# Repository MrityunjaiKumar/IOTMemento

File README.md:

# IOTMemento

## Introduction
This hardware was fabricated for AICTE Idea Lab FDP held at TI-CEPD, NSUT.
This repository is hosting tempalte code with Pinmapping and libraries information used during FDP. 
Also, An Android app is provided to view the data of the temperature form the hardware.
Features of this device are as follows:- 
1. Before wifi provisioning :- 

*  Rainbow pattern on RGB
*  Every 10 seconds all 12 petal leds will glow in linear fashion.

2. After wifi provisioning

* Rainbow pattern on RGB
* Play mario death tone every hour at 00 minute.
* Each of 12 petal leds will glow one after another in clockwise fashion, denoting complition of 5 minutes.
* Temperature sent to sincgrid cloud and data will be visible on sincgrid home app

### Design files

Editable files are located in Hardware folder

### Android APP
There is an Android application available at the play store for provisioning of the device (i.e. providing wifi ssid and passsword) and relaying the information.

Application can be located at https://play.google.com/store/apps/details?id=com.sincgrid.sincgridhome

Below are the steps needed to commision the device
1. Regsiter user
2. WiFi provision of the device
3. Regualr temperature update on the card

#### Registering the user
* After opening the app, Click on the Register button. 

* Fill in the details

* On provided email id, an OTP will be send. 

* After confirming the OTP you will be logged in into the application.

#### WiFi provision of the device

* On App side Click on the add button to start provisioning

* On device side, Press the button for 5 second, you will hear a buzzer beep that mark as confirmation of initiation of provisioning.

* To whatever the wifi you phone is connected, that SSID will be taken by default. To change this, you can switch the wifi form the phone.

* Please provide the credentials of the the ssid.

After this app will automatically add the device.

#### Regualr temperature update on the card
After every 15 minutes device will send the temperature data from LM75.

## Libraries used during FDP are :- 

* [esp32-Encrypt](https://github.com/josephpal/esp32-Encrypt.git)
* bblanchon/ArduinoJson
* [ESPAsyncWebServer](https://github.com/me-no-dev/ESPAsyncWebServer.git)
* [AsyncTCP](https://github.com/me-no-dev/AsyncTCP.git)
* [ESP32_AnalogWrite](https://github.com/ERROPiX/ESP32_AnalogWrite.git)
* [NTPClient](https://github.com/MrityunjaiKumar/NTPClient.git)
* [Tone](https://github.com/lbernstone/Tone.git)
* PubSubClient

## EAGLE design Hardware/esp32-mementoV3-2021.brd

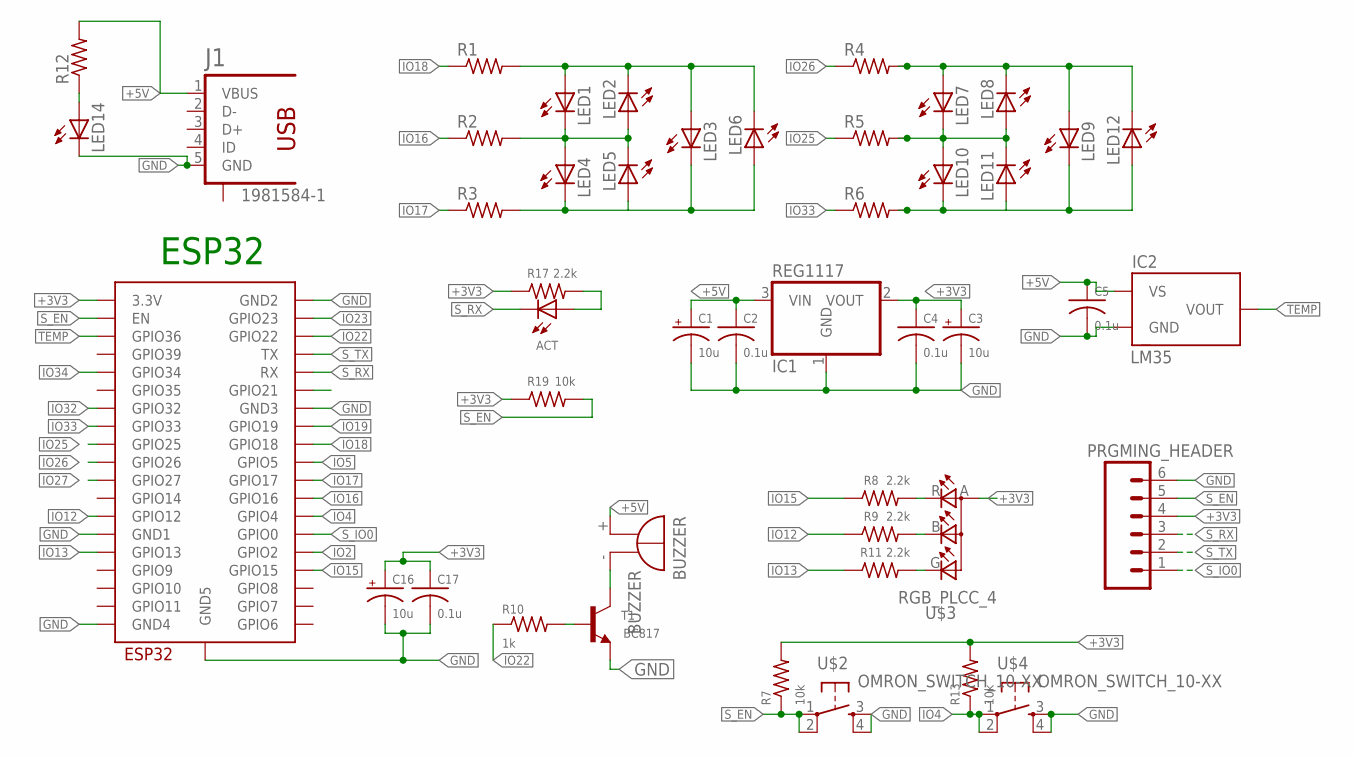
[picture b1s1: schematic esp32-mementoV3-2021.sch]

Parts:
ACT: LEDCHIPLED_1206; CHIPLED_1206
BUZZER: BUZZER; F/TMB
C1, C3, C16: 10u; B/3528-21R
C2, C4, C5, C17: 0.1u; C0603
ESP32_MODULE: ESP32-WROOM
IC1: REG1117; SOT223
IC2: LM35; TO92
J1: 1981584-1
LED1, LED2, LED3, LED4, LED5, LED6, LED7, LED8, LED9, LED10, LED11, LED12, LED14: LED1206; CHIPLED_1206
PRGMING_HEADER: M06; 06P
R1, R2, R3, R4, R5, R6, R12: RESISTOR0805; R0805
R7, R13: 10k; M0805
R8, R9, R11, R17: 2.2k; R0805
R10: 1k; M0805
R19: 10k; R0805
T1: BC817; SOT23-BEC
U$2, U$4: OMRON_SWITCH_10-XX; B3F-10XX
U$3: RGB_PLCC_4; PLCC-4

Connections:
+3V3: C3.+, C4.1, C16.+, C17.1, ESP32_MODULE.3V3 (3.3V), IC1.2 (VOUT), PRGMING_HEADER.4, R7.2, R13.2, R17.1, R19.1, U$3.A (A2)
+5V: BUZZER.+, C1.+, C2.1, C5.1, IC1.3 (VIN), IC2.VS, J1.1 (VBUS), R12.2
GND: C1.-, C2.2, C3.-, C4.2, C5.2, C16.-, C17.2, ESP32_MODULE.GND1, ESP32_MODULE.GND2, ESP32_MODULE.GND3, ESP32_MODULE.GND4, ESP32_MODULE.GND5, IC1.1 (GND), IC2.GND, J1.5 (GND), LED14.C, PRGMING_HEADER.6, T1.E, U$2.3 (S), U$2.4 (S1), U$4.3 (S), U$4.4 (S1)
IO2: ESP32_MODULE.IO2 (GPIO2)
IO4: ESP32_MODULE.IO4 (GPIO4), R13.1, U$4.1, U$4.2 (P1)
IO5: ESP32_MODULE.IO5 (GPIO5)
IO12: ESP32_MODULE.IO12 (GPIO12), R9.1
IO13: ESP32_MODULE.IO13 (GPIO13), R11.1
IO15: ESP32_MODULE.IO15 (GPIO15), R8.1
IO16: ESP32_MODULE.IO16 (GPIO16), R2.1
IO17: ESP32_MODULE.IO17 (GPIO17), R3.1
IO18: ESP32_MODULE.IO18 (GPIO18), R1.1
IO19: ESP32_MODULE.IO19 (GPIO19)
IO22: ESP32_MODULE.IO22 (GPIO22), R10.1
IO23: ESP32_MODULE.IO23 (GPIO23)
IO25: ESP32_MODULE.IO25 (GPIO25), R5.1
IO26: ESP32_MODULE.IO26 (GPIO26), R4.1
IO27: ESP32_MODULE.IO27 (GPIO27)
IO32: ESP32_MODULE.IO32 (GPIO32)
IO33: ESP32_MODULE.IO33 (GPIO33), R6.1
IO34: ESP32_MODULE.IO34 (GPIO34)
unnamed: LED1.A, LED2.C, LED3.A, LED6.C, R1.2
unnamed: LED1.C, LED2.A, LED4.A, LED5.C, R2.2
unnamed: LED3.C, LED4.C, LED5.A, LED6.A, R3.2
unnamed: LED7.A, LED8.C, LED9.A, LED12.C, R4.2
unnamed: LED7.C, LED8.A, LED10.A, LED11.C, R5.2
unnamed: LED9.C, LED10.C, LED11.A, LED12.A, R6.2
unnamed: BUZZER.-, T1.C
unnamed: R10.2, T1.B
unnamed: ACT.A, R17.2
unnamed: R8.2, U$3.R (CRED)
unnamed: R9.2, U$3.B (CBLUE)
unnamed: R11.2, U$3.G (CGREEN)
unnamed: LED14.A, R12.1
S_EN: ESP32_MODULE.EN, PRGMING_HEADER.5, R7.1, R19.2, U$2.1, U$2.2 (P1)
S_IO0: ESP32_MODULE.IO0 (GPIO0), PRGMING_HEADER.1
S_RX: ACT.C, ESP32_MODULE.RX, PRGMING_HEADER.3
S_TX: ESP32_MODULE.TX, PRGMING_HEADER.2
TEMP: ESP32_MODULE.SENSOR_VP (GPIO36), IC2.VOUT

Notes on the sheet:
ESP32

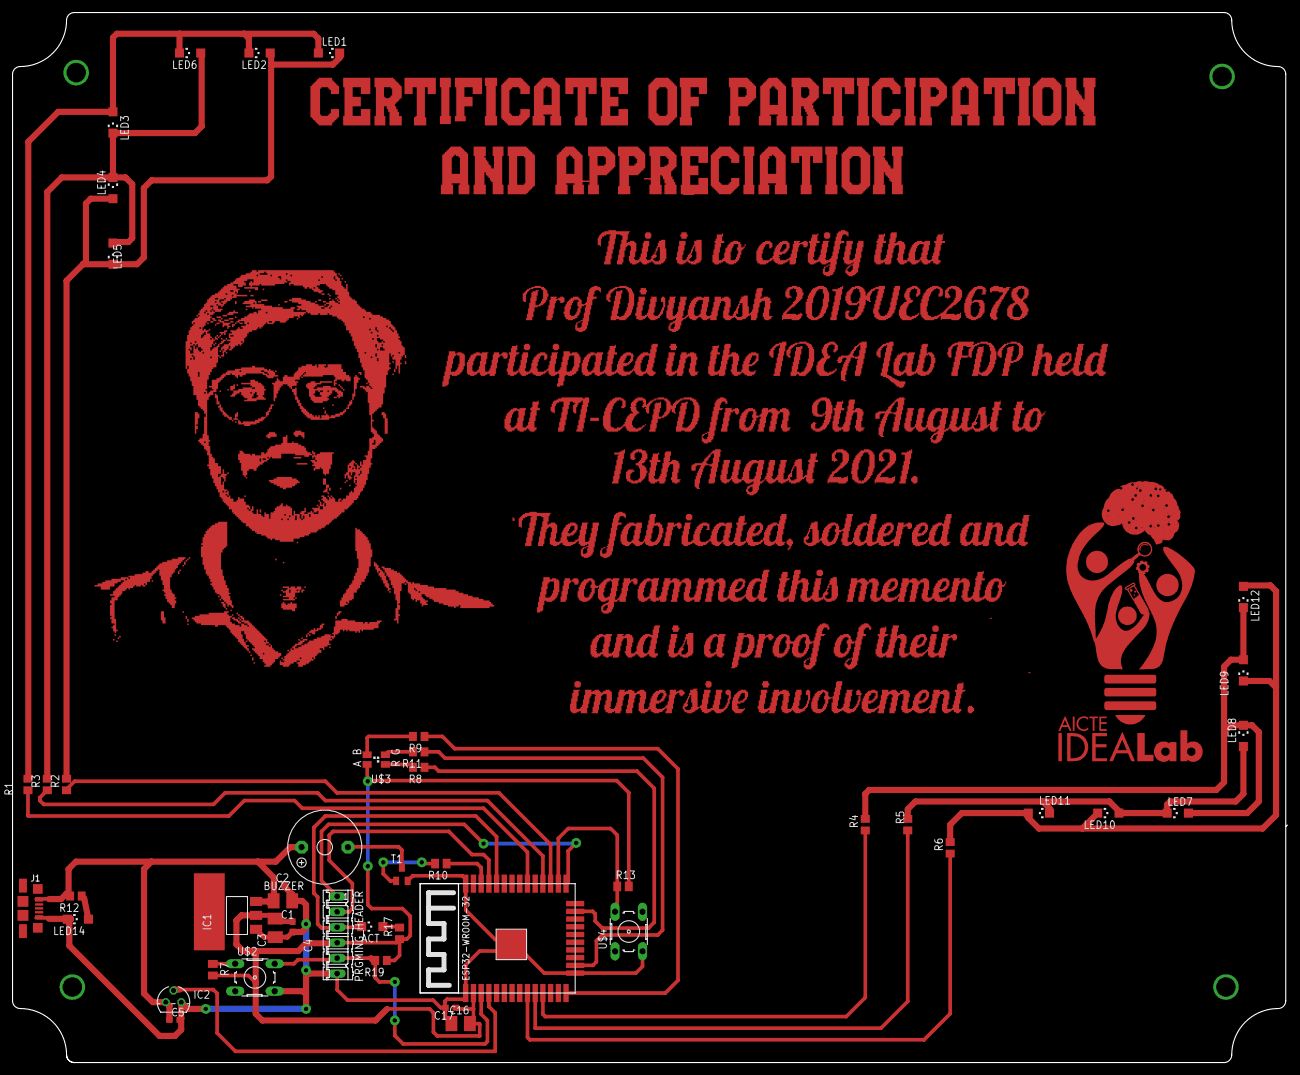
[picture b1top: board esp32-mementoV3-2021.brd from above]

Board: 2 copper layers, 209.6 x 172.8 mm, 46 parts (0 on the bottom side), 32 nets.

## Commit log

2021-08-24 Inital commit
2021-08-24 Schematic-Layout-TestCodes updated
2021-08-24 Libraries links added
2021-08-24 Design files added
